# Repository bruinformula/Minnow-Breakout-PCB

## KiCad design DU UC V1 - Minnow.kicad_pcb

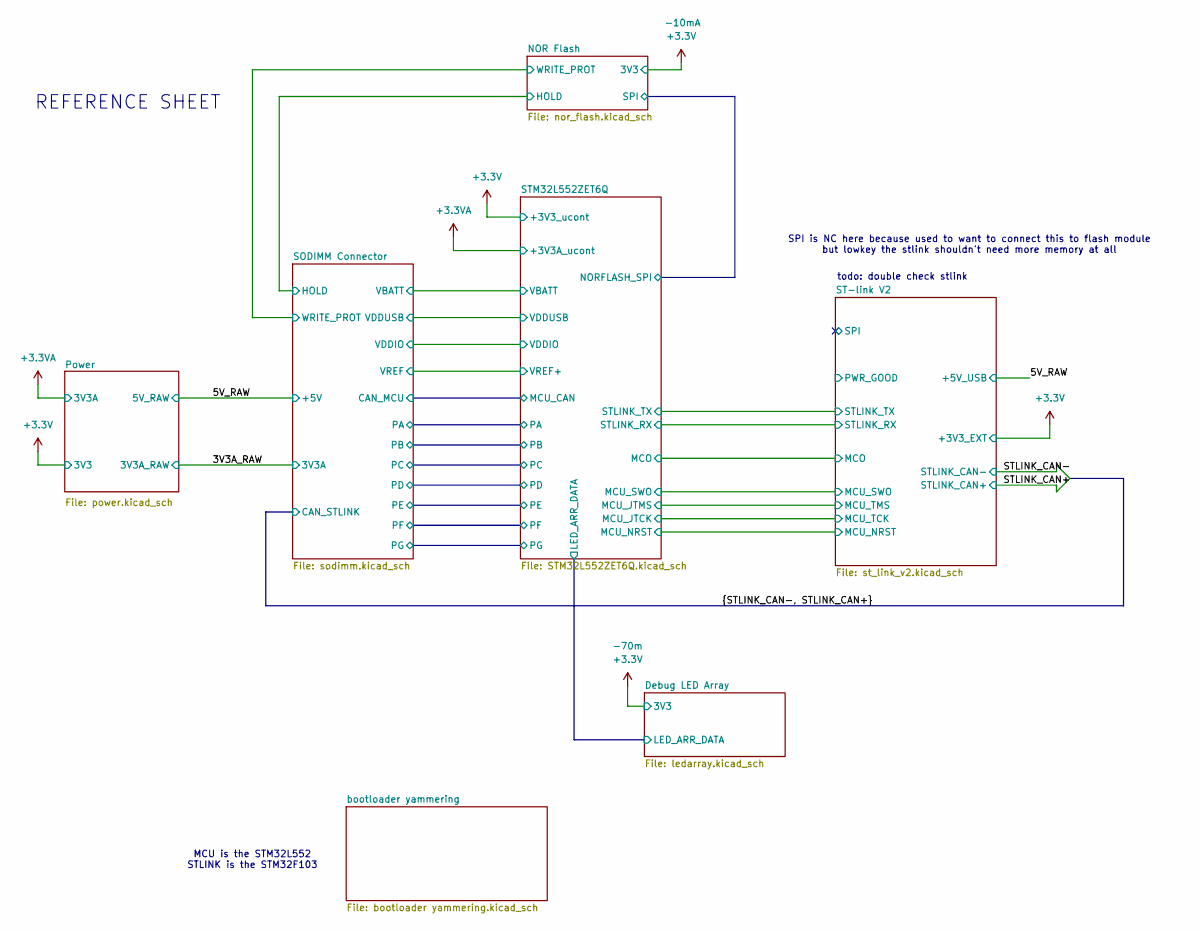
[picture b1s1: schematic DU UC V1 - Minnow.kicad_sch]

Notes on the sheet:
REFERENCE SHEET
SPI is NC here because used to want to connect this to flash module but lowkey the stlink shouldn't need more memory at all
todo: double check stlink
MCU is the STM32L552 STLINK is the STM32F103

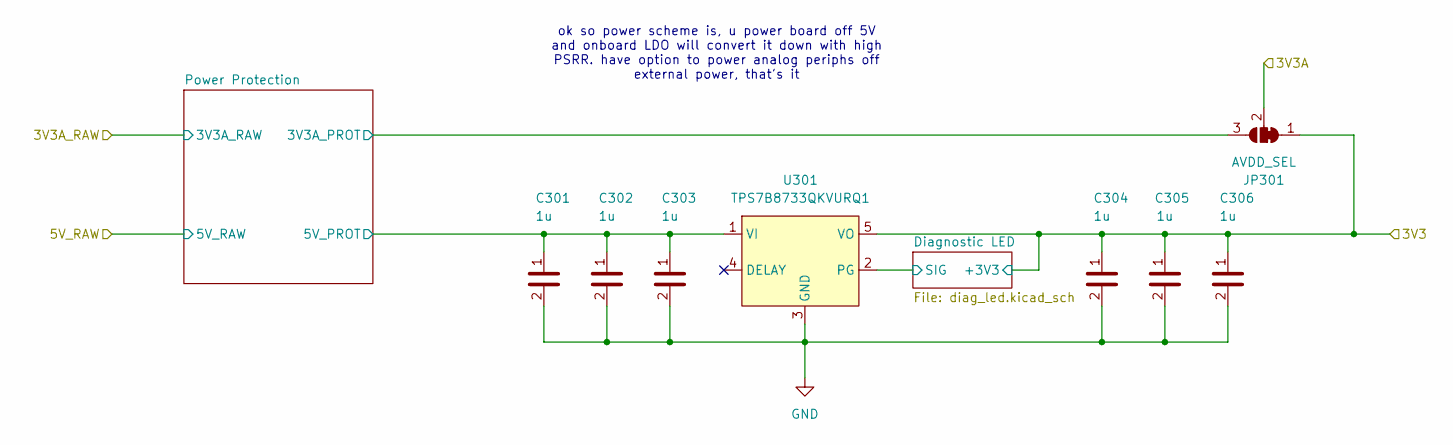
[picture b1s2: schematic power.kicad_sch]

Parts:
C301, C302, C303, C304, C305, C306: 1u; C_0402_1005Metric_Pad0.74x0.62mm_HandSolder; LCSC P/N C52923
JP301: AVDD_SEL; SolderJumper-3_P1.3mm_Bridged2Bar12_Pad1.0x1.5mm_NumberLabe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
U301: TPS7B8733QKVURQ1; TO-252-5_TabPin3; Manufacturer P/N TPS7B8733QKVURQ1; Digikey P/N 296-TPS7B8733QKVURQ1CT-ND

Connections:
+3.3V: C304.1, C305.1, C306.1, JP301.1 (A), U301.5 (VO); also elsewhere on the board
+3.3VA: JP301.2 (C); also elsewhere on the board
/Power/Diagnostic LED/SIG: U301.2 (PG); also elsewhere on the board
/Power/Power Protection/3V3A_PROT: JP301.3 (B); also elsewhere on the board
/Power/Power Protection/5V_PROT: C301.1, C302.1, C303.1, U301.1 (VI); also elsewhere on the board
GND: C301.2, C302.2, C303.2, C304.2, C305.2, C306.2, U301.3 (GND); also elsewhere on the board

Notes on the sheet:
ok so power scheme is, u power board off 5V and onboard LDO will convert it down with high PSRR. have option to power analog periphs off external power, that's it

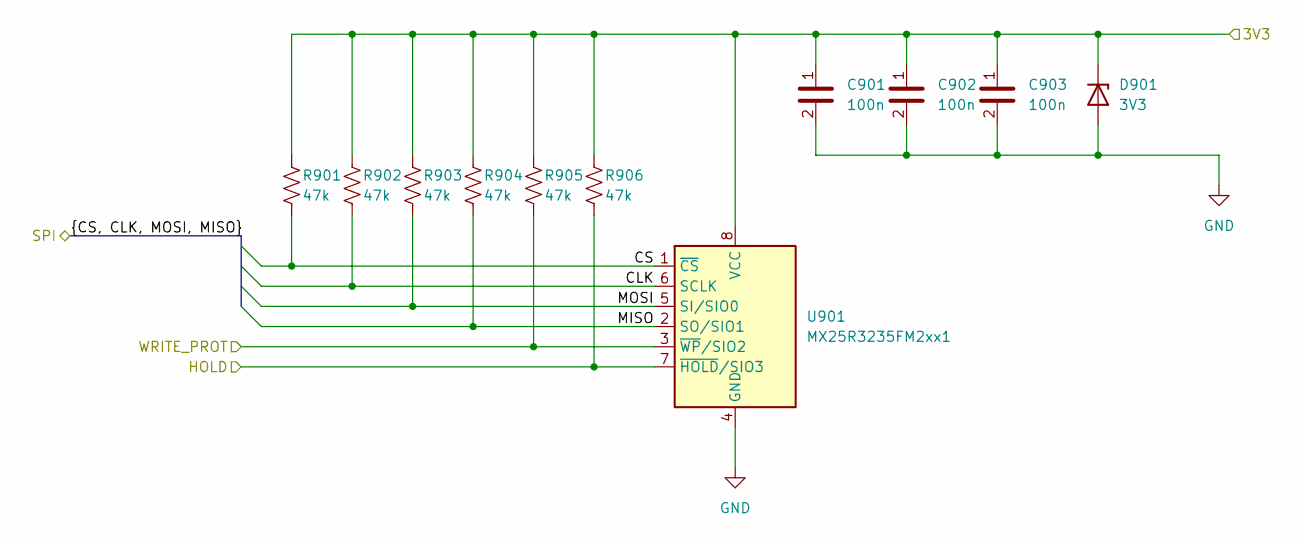
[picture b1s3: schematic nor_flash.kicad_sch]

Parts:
C901, C902, C903: 100n; C_0402_1005Metric_Pad0.74x0.62mm_HandSolder; LCSC P/N C307331
D901: 3V3; D_SOD-123; Manufacturer P/N BZT52C3V3; Digikey P/N 5399-BZT52C3V3TR-ND
R901, R902, R903, R904, R905, R906: 47k; R_0402_1005Metric_Pad0.72x0.64mm_HandSolder; Mouser P/N 708-RMCF0402FT47K0; Digikey P/N RMCF0402FT47K0CT-ND
U901: MX25R3235FM2xx1; SOIC-8_5.3x5.3mm_P1.27mm; Manufacturer P/N MX25R3235FM2IL0; Digikey P/N MX25R3235FM2IL0-ND

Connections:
+3.3V: C901.1, C902.1, C903.1, D901.1 (K), R901.2, R902.2, R903.2, R904.2, R905.2, R906.2, U901.8 (VCC); also elsewhere on the board
/NOR Flash/CLK: R902.1, U901.6 (SCLK); also elsewhere on the board
/NOR Flash/CS: R901.1, U901.1 (~CS); also elsewhere on the board
/NOR Flash/HOLD: R906.1, U901.7 (~HOLD/SIO3)
/NOR Flash/MISO: R904.1, U901.2 (SO/SIO1); also elsewhere on the board
/NOR Flash/MOSI: R903.1, U901.5 (SI/SIO0); also elsewhere on the board
/NOR Flash/WRITE_PROT: R905.1, U901.3 (~WP/SIO2)
GND: C901.2, C902.2, C903.2, D901.2 (A), U901.4 (GND); also elsewhere on the board

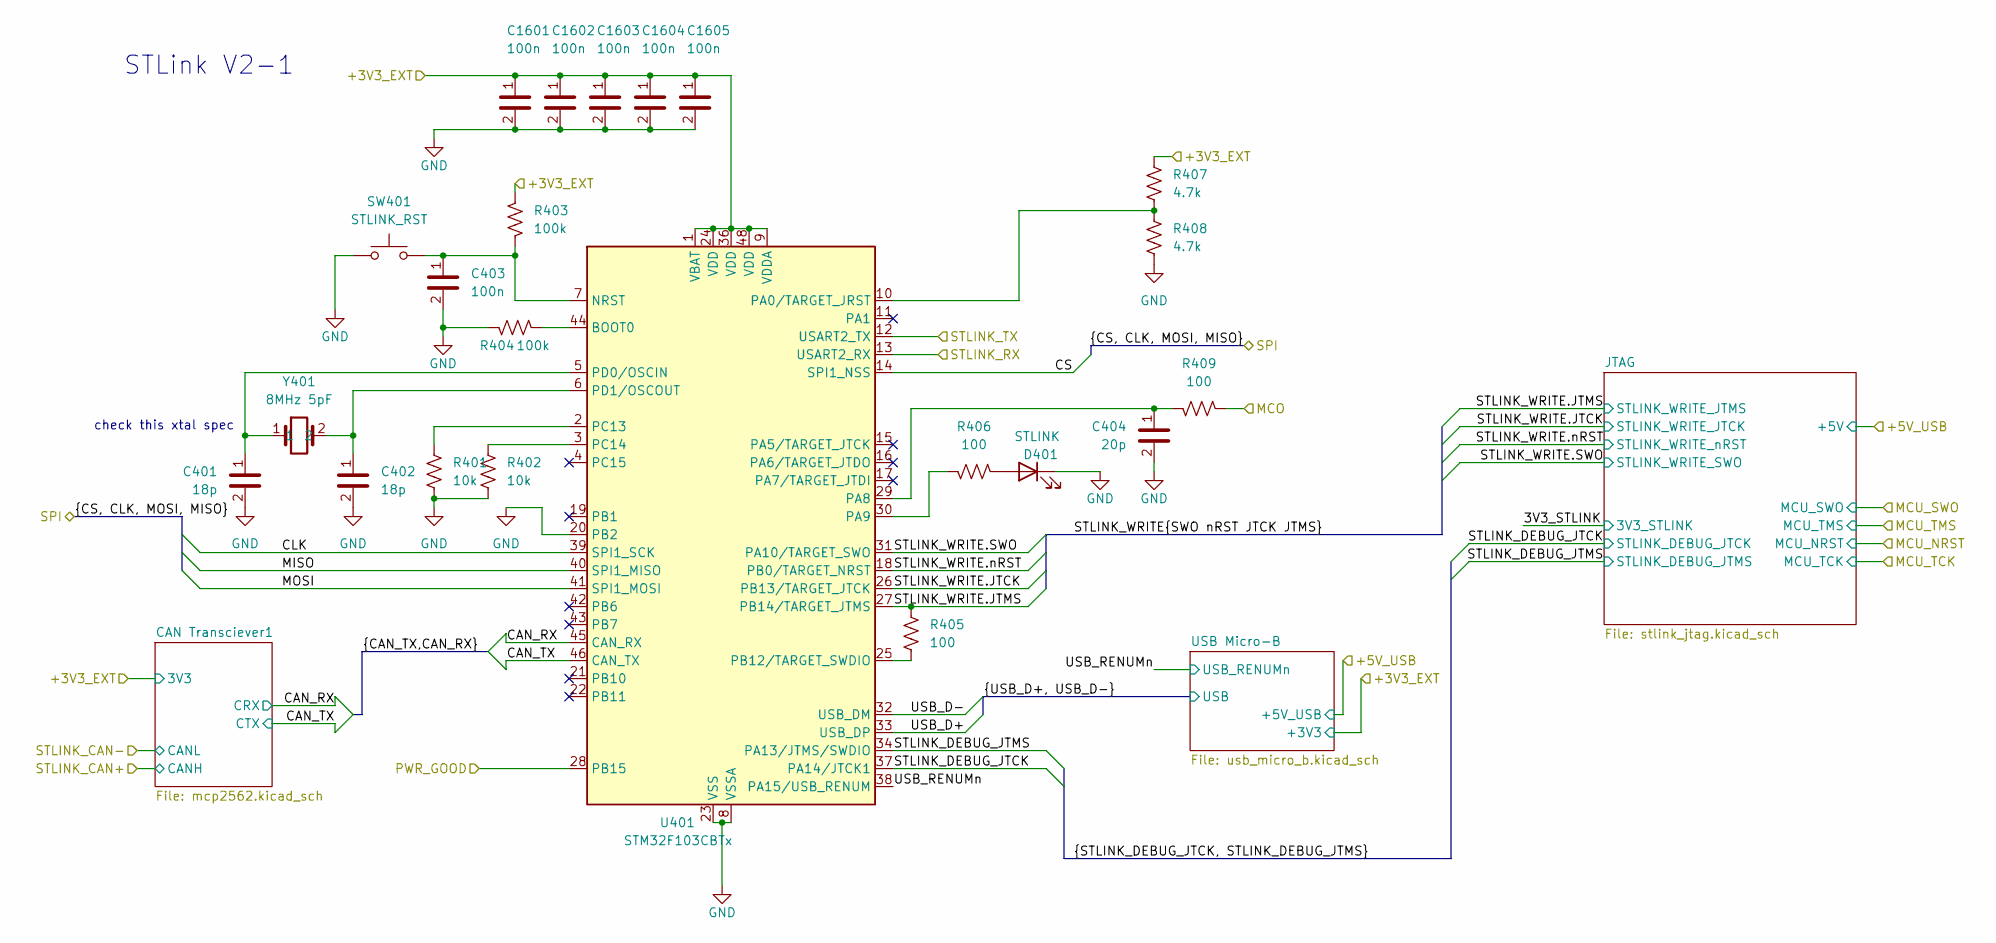
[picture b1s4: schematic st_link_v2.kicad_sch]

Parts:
C401, C402: 18p; C_0402_1005Metric_Pad0.74x0.62mm_HandSolder; LCSC P/N C1549
C403: 100n; C_0402_1005Metric_Pad0.74x0.62mm_HandSolder; LCSC P/N C307331
C404: 20p; C_0402_1005Metric_Pad0.74x0.62mm_HandSolder; LCSC P/N C1554
C1601, C1602, C1603, C1604, C1605: 100n; C_0402_1005Metric_Pad0.74x0.62mm_HandSolder; Mouser P/N 581-06035C104KAT2A; Digikey P/N 478-KGM15BR71H104KTCT-ND
D401: STLINK; LED_0603_1608Metric; Manufacturer_Part_Number KT-0603R; JLCPCB Basic Part Yes
R401, R402: 10k; R_0402_1005Metric_Pad0.72x0.64mm_HandSolder; Mouser P/N 708-RMCF0402FT10K0; Digikey P/N RMCF0402FT10K0CT-ND
R403, R404: 100k; R_0402_1005Metric_Pad0.72x0.64mm_HandSolder; Mouser P/N 708-RMCF0402FT100K; Digikey P/N RMCF0402FT100KCT-ND
R405: 100; R_0402_1005Metric_Pad0.72x0.64mm_HandSolder; Mouser P/N 708-RMCF0402FT4K70; Digikey P/N RMCF0402FT4K70CT-ND
R406, R409: 100; R_0402_1005Metric_Pad0.72x0.64mm_HandSolder; Mouser P/N 708-RMCF0402FT100R; Digikey P/N RMCF0402FT100RCT-ND
R407, R408: 4.7k; R_0402_1005Metric_Pad0.72x0.64mm_HandSolder; Mouser P/N 708-RMCF0402FT4K70; Digikey P/N RMCF0402FT4K70CT-ND
SW401: STLINK_RST; SW_Push_1P1T-SH_NO_CK_KMR2xxG
U401: STM32F103CBTx; LQFP-48_7x7mm_P0.5mm; LCSC P/N C8304
Y401: 8MHz 5pF; Crystal_SMD_5032-2Pin_5.0x3.2mm_HandSoldering; Manufacturer P/N AS-16.000-18-SMD-TR; Digikey P/N 4309-XC53G2-8.000-F20LJDTKCS-ND

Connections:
+3.3V: C1601.1, C1602.1, C1603.1, C1604.1, C1605.1, R403.2, R407.2, U401.1 (VBAT), U401.9 (VDDA), U401.24 (VDD), U401.36 (VDD), U401.48 (VDD); also elsewhere on the board
/ST-link V2/CAN_RX: U401.45 (CAN_RX); also elsewhere on the board
/ST-link V2/CAN_TX: U401.46 (CAN_TX); also elsewhere on the board
/ST-link V2/CLK: U401.39 (SPI1_SCK)
/ST-link V2/CS: U401.14 (SPI1_NSS)
/ST-link V2/MCO: R409.1; also elsewhere on the board
/ST-link V2/MISO: U401.40 (SPI1_MISO)
/ST-link V2/MOSI: U401.41 (SPI1_MOSI)
/ST-link V2/PWR_GOOD: U401.28 (PB15)
/ST-link V2/STLINK_DEBUG_JTCK: U401.37 (PA14/JTCK1); also elsewhere on the board
/ST-link V2/STLINK_DEBUG_JTMS: U401.34 (PA13/JTMS/SWDIO); also elsewhere on the board
/ST-link V2/STLINK_WRITE.JTCK: U401.26 (PB13/TARGET_JTCK); also elsewhere on the board
/ST-link V2/STLINK_WRITE.JTMS: R405.2, U401.27 (PB14/TARGET_JTMS); also elsewhere on the board
/ST-link V2/STLINK_WRITE.SWO: U401.31 (PA10/TARGET_SWO); also elsewhere on the board
/ST-link V2/STLINK_WRITE.nRST: U401.18 (PB0/TARGET_NRST); also elsewhere on the board
/ST-link V2/USB_D+: U401.33 (USB_DP); also elsewhere on the board
/ST-link V2/USB_D-: U401.32 (USB_DM); also elsewhere on the board
/ST-link V2/USB_RENUMn: U401.38 (PA15/USB_RENUM); also elsewhere on the board
/STM32L552ZET6Q/USART1_RX: U401.13 (USART2_RX); also elsewhere on the board
/STM32L552ZET6Q/USART1_TX: U401.12 (USART2_TX); also elsewhere on the board
GND: C401.2, C402.2, C403.2, C404.2, C1601.2, C1602.2, C1603.2, C1604.2, C1605.2, D401.1 (K), R401.1, R402.1, R404.2, R408.1, SW401.1, U401.8 (VSSA), U401.20 (PB2), U401.23 (VSS), U401.35 (VSS), U401.47 (VSS); also elsewhere on the board
unnamed: D401.2 (A), R406.1
unnamed: R404.1, U401.44 (BOOT0)
unnamed: C403.1, R403.1, SW401.2, U401.7 (NRST)
unnamed: R407.1, R408.2, U401.10 (PA0/TARGET_JRST)
unnamed: C404.1, R409.2, U401.29 (PA8)
unnamed: R406.2, U401.30 (PA9)
unnamed: R405.1, U401.25 (PB12/TARGET_SWDIO)
unnamed: R401.2, U401.2 (PC13)
unnamed: R402.2, U401.3 (PC14)
unnamed: C401.1, U401.5 (PD0/OSCIN), Y401.1
unnamed: C402.1, U401.6 (PD1/OSCOUT), Y401.2

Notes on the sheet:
STLink V2-1
check this xtal spec

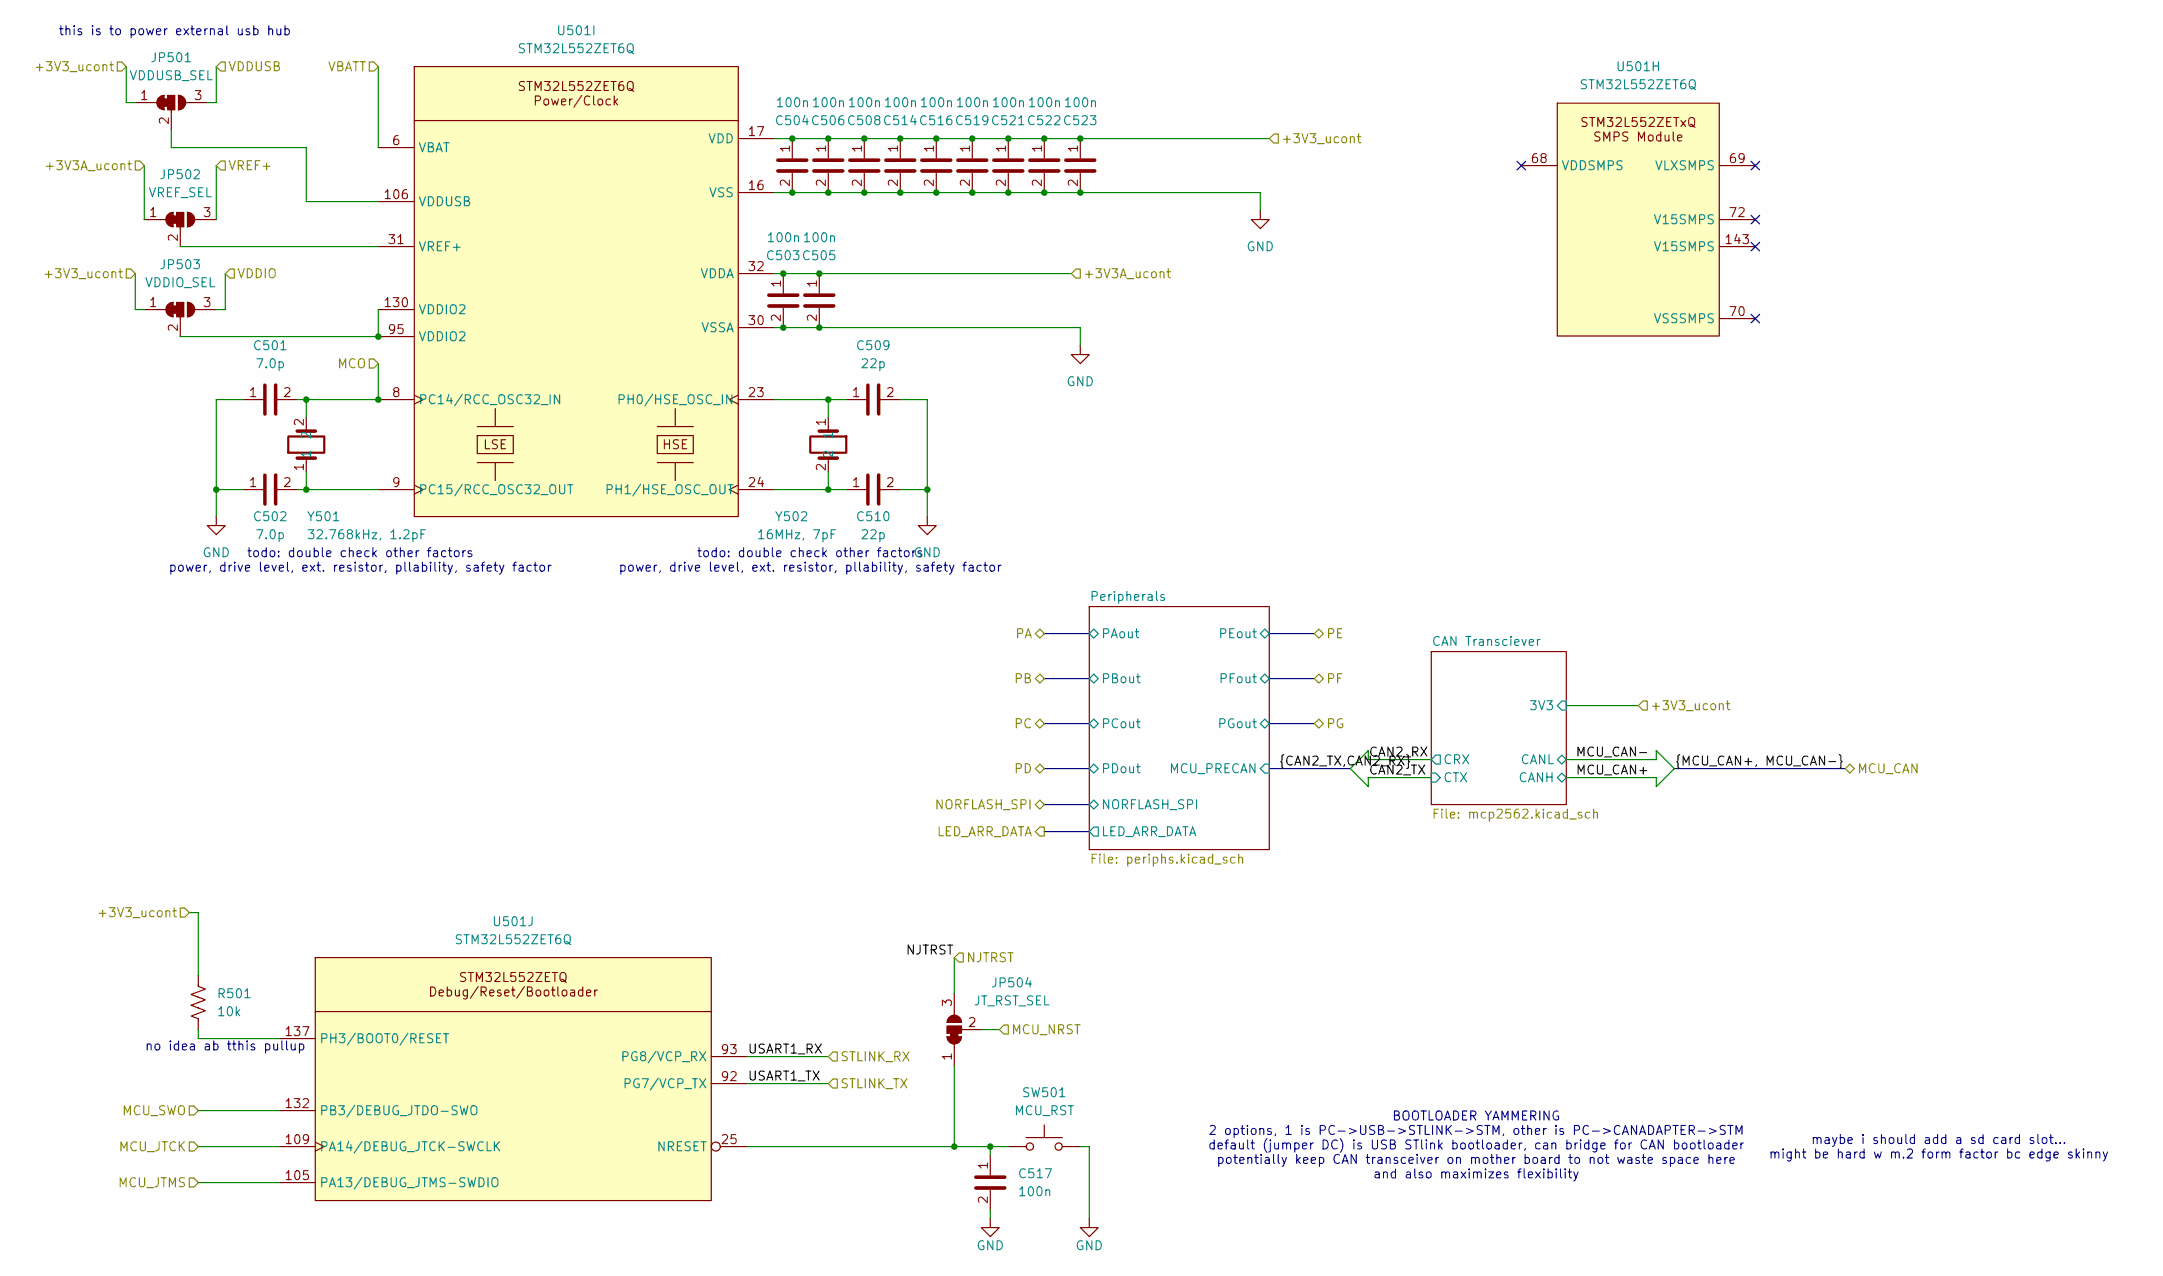
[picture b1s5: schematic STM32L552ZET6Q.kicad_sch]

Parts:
C501, C502: 7.0p; C_0603_1608Metric_Pad1.08x0.95mm_HandSolder; Mouser P/N 581-06035A7R0JAT2A
C503, C504, C505, C506, C508, C514, C516, C519, C521, C522, C523: 100n; C_0402_1005Metric_Pad0.74x0.62mm_HandSolder; LCSC P/N C307331
C509, C510: 22p; C_0402_1005Metric_Pad0.74x0.62mm_HandSolder; LCSC P/N C1555
C517: 100n; C_0603_1608Metric_Pad1.08x0.95mm_HandSolder; Mouser P/N 581-06035C104KAT2A; Digikey P/N 478-KGM15BR71H104KTCT-ND
JP501: VDDUSB_SEL; SolderJumper-3_P1.3mm_Bridged2Bar12_Pad1.0x1.5mm_NumberLabe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
JP502: VREF_SEL; SolderJumper-3_P1.3mm_Bridged2Bar12_Pad1.0x1.5mm_NumberLabe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
JP503: VDDIO_SEL; SolderJumper-3_P1.3mm_Bridged2Bar12_Pad1.0x1.5mm_NumberLabe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
JP504: JT_RST_SEL; SolderJumper-3_P1.3mm_Bridged2Bar12_Pad1.0x1.5mm_NumberLabe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
R501: 10k; R_0402_1005Metric_Pad0.72x0.64mm_HandSolder; Mouser P/N 708-RMCF0402FT10K0; Digikey P/N RMCF0402FT10K0CT-ND
SW501: MCU_RST; SW_Push_1P1T-SH_NO_CK_KMR2xxG
U501: STM32L552ZET6Q; LQFP-144_20x20mm_P0.5mm; Manufacturer P/N STM32L552ZET6Q; LCSC P/N TO ORDER
Y501: 32.768kHz, 1.2pF; Crystal_SMD_2012-2Pin_2.0x1.2mm_HandSoldering; Manufacturer P/N CM8V-T1A-32.768KHZ-4PF-20PPM-TA-QC; Digikey P/N 2195-CM8V-T1A-32.768KHZ-4PF-20PPM-TA-QC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
Y502: 16MHz, 7pF; ABM3-16.000MHZ-D2Y-T; Manufacturer P/N ABM3-16.000MHZ-D2Y-T; Digikey P/N 535-10638-1-ND

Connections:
+3.3V: C504.1, C506.1, C508.1, C514.1, C516.1, C519.1, C521.1, C522.1, C523.1, JP501.1 (A), JP503.1 (A), R501.2, U501.17 (VDD), U501.38 (VDD), U501.49 (VDD), U501.59 (VDD), U501.73 (VDD), U501.84 (VDD), U501.108 (VDD), U501.121 (VDD), U501.144 (VDD); also elsewhere on the board
+3.3VA: C503.1, C505.1, JP502.1 (A), U501.32 (VDDA); also elsewhere on the board
/SODIMM Connector/VBATT: U501.6 (VBAT); also elsewhere on the board
/SODIMM Connector/VDDIO: JP503.3 (B); also elsewhere on the board
/SODIMM Connector/VDDUSB: JP501.3 (B); also elsewhere on the board
/SODIMM Connector/VREF: JP502.3 (B); also elsewhere on the board
/ST-link V2/MCO: C501.2, U501.8 (PC14/RCC_OSC32_IN), Y501.2; also elsewhere on the board
/ST-link V2/MCU_NRST: JP504.2 (C); also elsewhere on the board
/ST-link V2/MCU_SWO: U501.132 (PB3/DEBUG_JTDO-SWO); also elsewhere on the board
/ST-link V2/MCU_TCK: U501.109 (PA14/DEBUG_JTCK-SWCLK); also elsewhere on the board
/ST-link V2/MCU_TMS: U501.105 (PA13/DEBUG_JTMS-SWDIO); also elsewhere on the board
/STM32L552ZET6Q/NJTRST: JP504.3 (B)
/STM32L552ZET6Q/USART1_RX: U501.93 (PG8/VCP_RX); also elsewhere on the board
/STM32L552ZET6Q/USART1_TX: U501.92 (PG7/VCP_TX); also elsewhere on the board
GND: C501.1, C502.1, C503.2, C504.2, C505.2, C506.2, C508.2, C509.2, C510.2, C514.2, C516.2, C517.2, C519.2, C521.2, C522.2, C523.2, SW501.1, U501.16 (VSS), U501.30 (VSSA), U501.37 (VSS), U501.48 (VSS), U501.58 (VSS), U501.71 (VSS), U501.83 (VSS), U501.94 (VSS), U501.107 (VSS), U501.120 (VSS), U501.129 (VSS), U501.142 (VSS); also elsewhere on the board
unnamed: JP501.2 (C), U501.106 (VDDUSB)
unnamed: JP502.2 (C), U501.31 (VREF+)
unnamed: JP503.2 (C), U501.95 (VDDIO2), U501.130 (VDDIO2)
unnamed: C517.1, JP504.1 (A), SW501.2, U501.25 (NRESET)
unnamed: C502.2, U501.9 (PC15/RCC_OSC32_OUT), Y501.1
unnamed: C509.1, U501.23 (PH0/HSE_OSC_IN), Y502.1
unnamed: C510.1, U501.24 (PH1/HSE_OSC_OUT), Y502.2
unnamed: R501.1, U501.137 (PH3/BOOT0/RESET)

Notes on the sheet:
todo: double check other factors power, drive level, ext. resistor, pllability, safety factor
this is to power external usb hub
maybe i should add a sd card slot... might be hard w m.2 form factor bc edge skinny
BOOTLOADER YAMMERING 2 options, 1 is PC->USB->STLINK->STM, other is PC->CANADAPTER->STM default (jumper DC) is USB STlink bootloader, can bridge for CAN bootloader potentially keep CAN transceiver on mother board to not waste space here and also maximizes flexibility
no idea ab tthis pullup

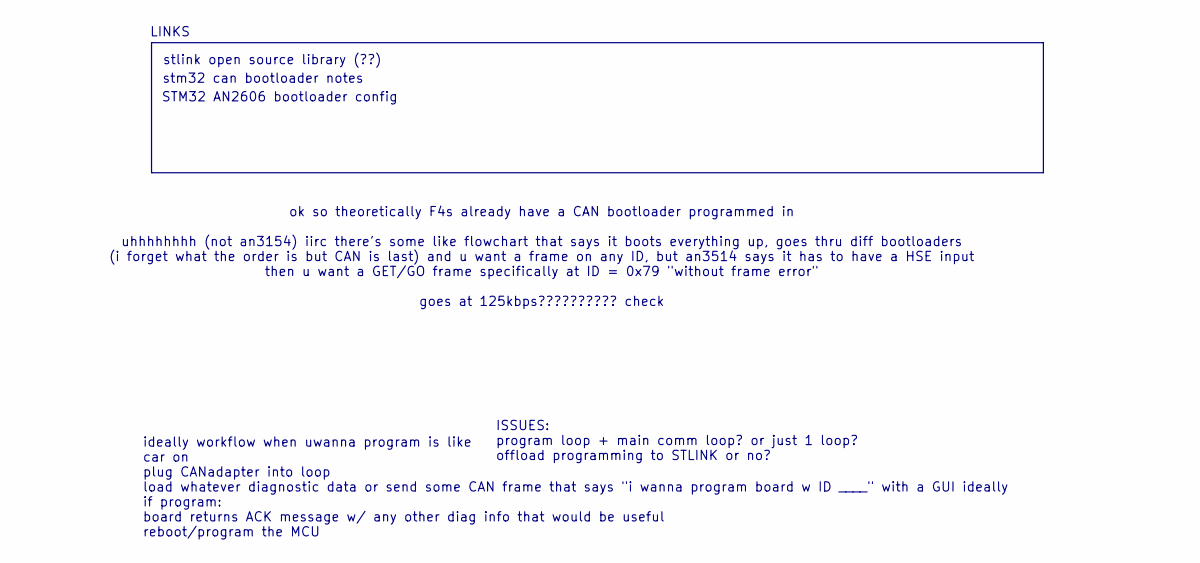
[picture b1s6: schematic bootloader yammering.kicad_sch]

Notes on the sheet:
LINKS
stlink open source library (??)
stm32 can bootloader notes
STM32 AN2606 bootloader config
ideally workflow when uwanna program is like car on plug CANadapter into loop load whatever diagnostic data or send some CAN frame that says "i wanna program board w ID ____" with a GUI ideally if program: board returns ACK message w/ any other diag info that would be useful reboot/program the MCU
ok so theoretically F4s already have a CAN bootloader programmed in uhhhhhhhh (not an3154) iirc there's some like flowchart that says it boots everything up, goes thru diff bootloaders (i forget what the order is but CAN is last) and u want a frame on any ID, but an3514 says it has to have a HSE in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
ISSUES: program loop + main comm loop? or just 1 loop? offload programming to STLINK or no?

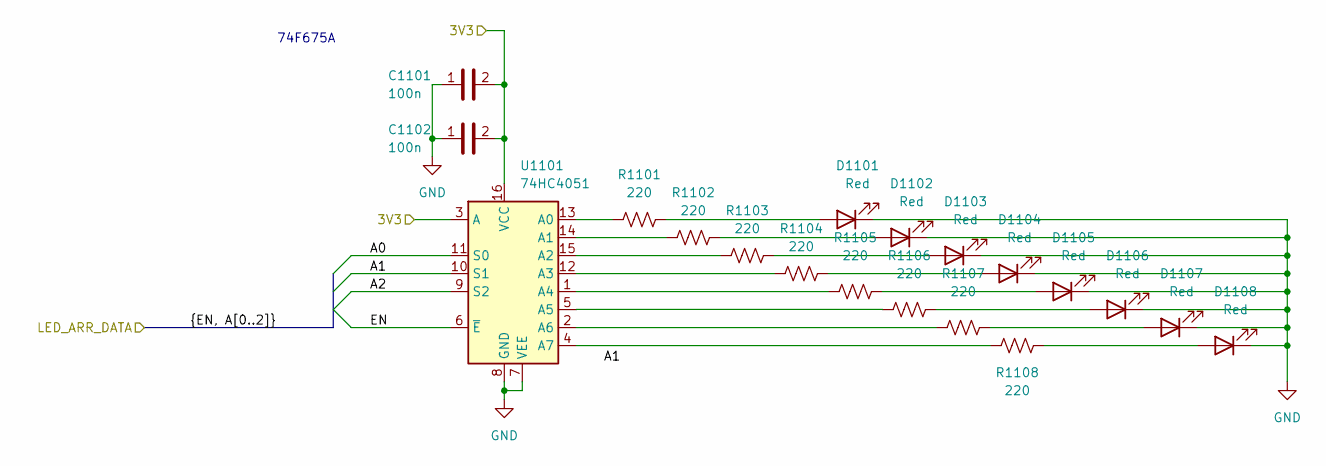
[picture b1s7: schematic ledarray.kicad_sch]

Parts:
C1101, C1102: 100n; C_0402_1005Metric_Pad0.74x0.62mm_HandSolder; LCSC P/N C307331
D1101, D1102, D1103, D1104, D1105, D1106, D1107, D1108: Red; D_0603_1608Metric_Pad1.05x0.95mm_HandSolder; Mouser P/N 720-LRQ976.01; Digikey P/N 475-LRQ976.01-P2R2-1CT-ND
R1101, R1102, R1103, R1104, R1105, R1106, R1107, R1108: 220; R_0402_1005Metric_Pad0.72x0.64mm_HandSolder; Mouser P/N 708-RMCF0402FT220R; Digikey P/N RMCF0402FT220RCT-ND
U1101: 74HC4051; TSSOP-16_4.4x5mm_P0.65mm

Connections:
+3.3V: C1101.2, C1102.2, U1101.3 (A), U1101.16 (VCC); also elsewhere on the board
/Debug LED Array/A0: U1101.11 (S0); also elsewhere on the board
/Debug LED Array/A1: U1101.10 (S1); also elsewhere on the board
/Debug LED Array/A2: U1101.9 (S2); also elsewhere on the board
/Debug LED Array/EN: U1101.6 (~E); also elsewhere on the board
GND: C1101.1, C1102.1, D1101.1 (K), D1102.1 (K), D1103.1 (K), D1104.1 (K), D1105.1 (K), D1106.1 (K), D1107.1 (K), D1108.1 (K), U1101.7 (VEE), U1101.8 (GND); also elsewhere on the board
unnamed: D1101.2 (A), R1101.2
unnamed: D1102.2 (A), R1102.2
unnamed: D1103.2 (A), R1103.2
unnamed: D1104.2 (A), R1104.2
unnamed: D1105.2 (A), R1105.2
unnamed: D1106.2 (A), R1106.2
unnamed: D1107.2 (A), R1107.2
unnamed: D1108.2 (A), R1108.2
unnamed: R1101.1, U1101.13 (A0)
unnamed: R1102.1, U1101.14 (A1)
unnamed: R1103.1, U1101.15 (A2)
unnamed: R1104.1, U1101.12 (A3)
unnamed: R1105.1, U1101.1 (A4)
unnamed: R1106.1, U1101.5 (A5)
unnamed: R1107.1, U1101.2 (A6)
unnamed: R1108.1, U1101.4 (A7)

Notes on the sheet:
74F675A

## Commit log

2025-08-05 v1 done
2025-08-05 jk im stupid forgot to route the flash
2025-10-01 fixed like a bunch of things, power and new xcvr and lights and other goodies, also started layout
2025-10-01 quicksave on some R.S. T.S. (mostly layout changes, small pin changes for better routing)
2025-10-03 laid out most of power, main xcvr, prob some other stuff
2025-10-04 i fucken rerouted everything and redid the pinout like 3x, half routed GPIOs
2025-10-04 holy fucking stupid ass why did u put this upon urself
2025-10-07 fucking shit bro i like expanded the board by 1mm and it still has no room fuck this bitchass crystal
2025-10-10 slimed out gpio conns, changed to 6layer
2025-10-15 i dont know what changed. dont ask me.
2025-12-24 small schematic changes, need to reroute
